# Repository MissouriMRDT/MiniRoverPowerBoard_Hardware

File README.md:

# MiniRoverPowerBoard_Hardware
This repository holds the files to build a Mini Rover that is used during PR events.

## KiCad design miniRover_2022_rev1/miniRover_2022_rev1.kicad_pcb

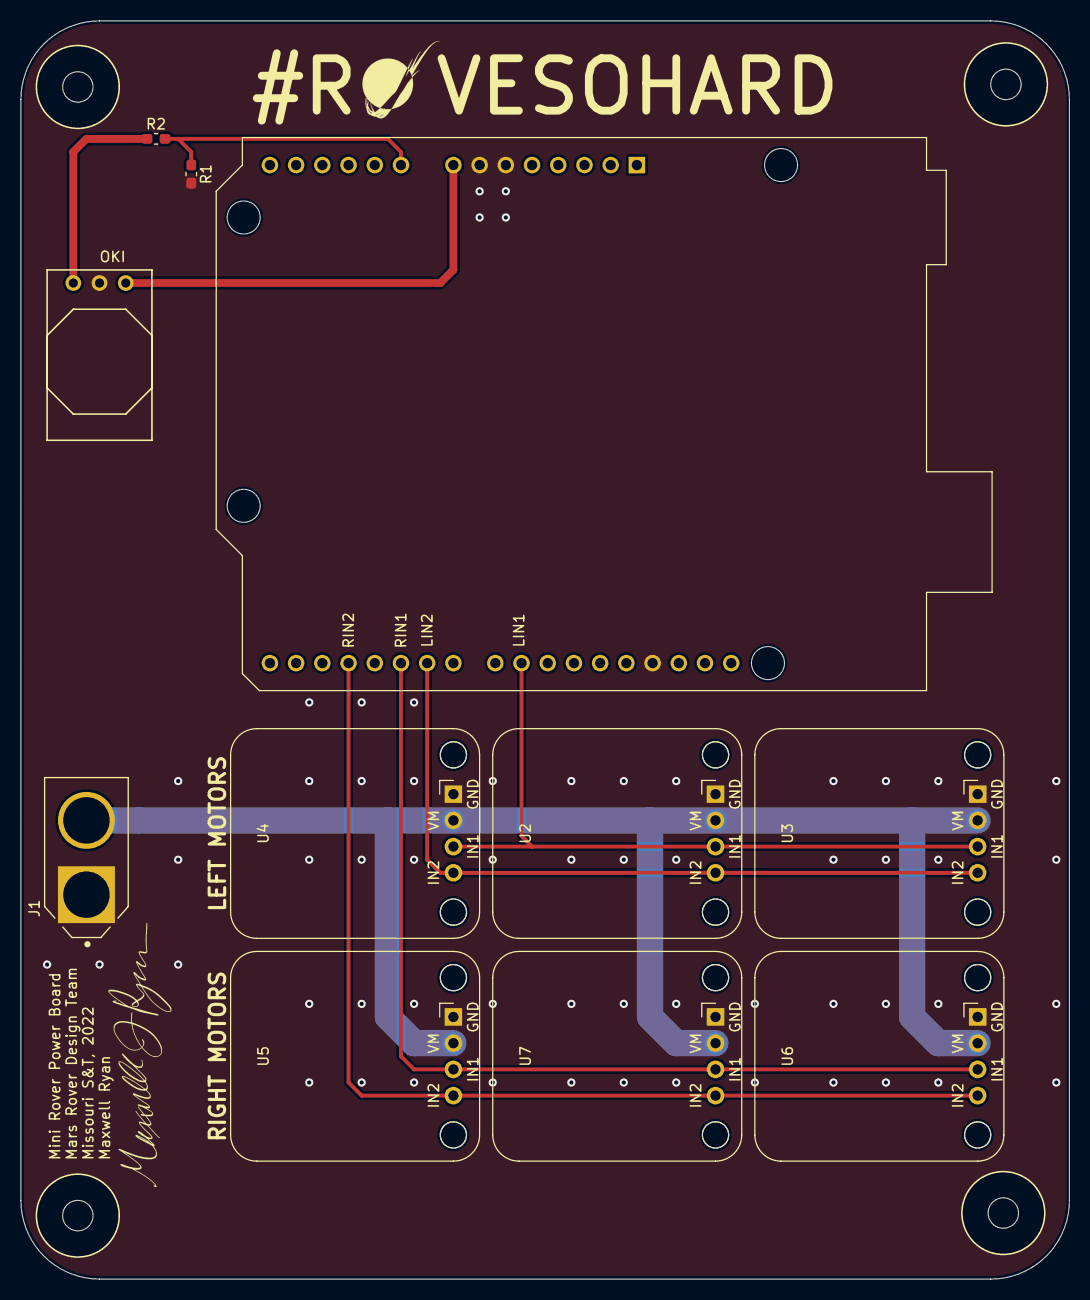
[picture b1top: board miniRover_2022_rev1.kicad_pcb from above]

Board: 2 copper layers, 101.6 x 121.9 mm, 11 parts (1 on the bottom side), 8 nets.

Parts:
A1: Arduino_UNO_R3; Arduino_UNO_R3_WithMountingHoles
J1: XT60-M; AMASS_XT60-M
R1: 1k; R_0603_1608Metric_Pad1.05x0.95mm_HandSolder
R2: 2k; R_0603_1608Metric_Pad1.05x0.95mm_HandSolder
U1: OKI; OKI_Horizontal
U2, U3, U4, U5, U6, U7: DRV8871-Breakout-PCB

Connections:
+5V: A1.8, U1.3
+12V: J1.2, R2.1, U1.1, U2.2, U3.2, U4.2, U5.2, U6.2, U7.2
/motorControllers/LIN1: A1.24, U2.3, U3.3, U4.3
/motorControllers/LIN2: A1.21, U2.4, U3.4, U4.4
/motorControllers/RIN1: A1.20, U5.3, U6.3, U7.3
/motorControllers/RIN2: A1.18, U5.4, U6.4, U7.4
GND: A1.6, A1.7, A1.29, J1.1, R1.2, U1.2, U2.1, U3.1, U4.1, U5.1, U6.1, U7.1
unnamed: A1.9, R1.1, R2.2

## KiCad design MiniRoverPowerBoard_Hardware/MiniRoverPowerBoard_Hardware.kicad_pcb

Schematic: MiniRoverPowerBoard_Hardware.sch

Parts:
B1: Buzzer; BUZZER_SMI_1324_TW_5V_2_R
C1, C4, C8, C9, C10, C11, C12: 10u; C_0603_1608Metric_Pad1.05x0.95mm_HandSolder
C2: 1n; C_0603_1608Metric_Pad1.05x0.95mm_HandSolder
C5, C6: 470u; CP_Radial_D8.0mm_P3.50mm
Conn1, Conn2, Conn3, Conn4: AndersonPP; Anderson_2_Horizontal_Side_by_Side
Conn5: E_STOP; MOLEX_SL_02_Vertical
Conn6: Molex_SL_07; MOLEX_SL_07_Vertical
Conn7: Molex_SL_03; MOLEX_SL_03_Vertical
Conn8: Molex_SL_02; MOLEX_SL_02_Vertical
Conn9, Conn10: Molex_SL_04; MOLEX_SL_04_Vertical
D1, D9: 4.7V_Zener; D_SOD-123
D2, D3, D4, D5, D6, D10, D11: LED; LED_0603_1608Metric_Pad1.05x0.95mm_HandSolder
D8: D_Schottky; D_0603_1608Metric_Pad1.05x0.95mm_HandSolder
F1: 35A_Fuse; ATC_Fuse_Block
L2: 47uH; CP_Radial_D5.0mm_P2.00mm
Q1, Q2, Q4: Q_NMOS_GSD; SOT-323_SC-70_Handsoldering
Q3: Q_PMOS_GDS; TO-252-2
R1, R2, R3, R4, R5, R6: 1k; R_0603_1608Metric_Pad1.05x0.95mm_HandSolder
R7, R10, R13, R14, R25: 10k; R_0603_1608Metric_Pad1.05x0.95mm_HandSolder
R8, R22: 21k; R_0603_1608Metric_Pad1.05x0.95mm_HandSolder
R9, R23: 26.7k; R_0603_1608Metric_Pad1.05x0.95mm_HandSolder
R11: 30k; R_0603_1608Metric_Pad1.05x0.95mm_HandSolder
R12: 13k; R_0603_1608Metric_Pad1.05x0.95mm_HandSolder
R15, R26: 0; R_0603_1608Metric_Pad1.05x0.95mm_HandSolder
R16, R17, R19, R20, R21, R24: 510; R_0603_1608Metric_Pad1.05x0.95mm_HandSolder
R18: 100; R_0603_1608Metric_Pad1.05x0.95mm_HandSolder
SW1: Relay_SPST; MOLEX_SL_04_Vertical
SW2, SW3: SW_Push; SW_SPST_TL3305A
U1, U2: VNH5019A_E; MultiPowerSO_30
U3: ACS722xLCTR-40AU; SOIC-8_3.9x4.9mm_P1.27mm
U5: AP1509; SOIC-8_3.9x4.9mm_P1.27mm
U6: ARDUINO_MICRO_SHIELD

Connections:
+3V3: C1.2, R18.1, U1.5, U1.6, U1.9, U2.5, U2.6, U2.9, U3.8 (VCC), U6.3.3V
+5V: B1.1, C8.1, Conn6.1, Conn8.1, L2.2, R17.1, R26.2, SW1.2, SW2.1, SW3.1, U5.3
/5V_R: R26.1, U6.5V
/PVDD_IN1: Conn1.2, Conn2.2, F1.2
/PVDD_IN2: F1.1, U3.1 (IP+), U3.2 (IP+)
/PVDD_IN3: Q3.3, R11.1, SW1.3, U3.3 (IP-), U3.4 (IP-)
/VIN_R: R15.1, U6.VI
ACT_PWR: C5.1, C6.1, C9.1, C10.1, C11.1, C12.1, Conn9.1, Conn9.2, Conn10.1, Conn10.2, Q3.2, R16.1, R22.1, U1.3, U1.12, U1.13, U1.23, U1.32, U2.3, U2.12, U2.13, U2.23, U2.32
BUZZER_EN: Q4.1, R25.2, U6.2
CONTROLLER_ATT: Conn6.6, U6.A1
CONTROLLER_CLK: Conn6.4, U6.13
CONTROLLER_CMD: Conn6.5, U6.A0
CONTROLLER_DAT: Conn6.7, U6.A2
ESTOP_EN: Conn5.1, U6.3
GND: C1.1, C2.1, C4.2, C5.2, C6.2, C8.2, C9.2, C10.2, C11.2, C12.2, Conn1.1, Conn2.1, Conn6.2, Conn7.3, Conn8.2, Conn9.3, Conn9.4, Conn10.3, Conn10.4, D1.2, D2.1, D3.1, D4.1, D5.1, D6.1, D8.2, D9.2, D10.1, D11.1, Q1.2, Q2.2, Q4.2, R7.2, R9.2, R10.2, R13.2, R14.2, R23.2, R25.1, U1.18, U1.19, U1.20, U1.26, U1.27, U1.28, U2.18, U2.19, U2.20, U2.26, U2.27, U2.28, U3.5 (GND), U5.4, U5.5, U5.6, U5.7, U5.8, U6.GND
IN_A1: R1.1, U6.5
IN_A2: R4.1, U6.8
IN_B1: R3.1, U6.7
IN_B2: R6.1, U6.10
LEFT_PWM: R2.1, U6.6
LEFT_SW: R13.1, SW2.2, U6.12
LOGIC_PWR: C4.1, R8.1, R15.2, SW1.4, U5.1
LOG_SW_EN: Q1.1, R7.1, U6.4
unnamed: B1.2, Q4.3
unnamed: C2.2, U3.6 (BW_SEL)
unnamed: Conn5.2, Q2.1, R10.1
unnamed: D2.2, R16.2
unnamed: D3.2, R17.2
unnamed: D4.2, R18.2
unnamed: D5.2, R19.2
unnamed: D6.2, R20.2
unnamed: D8.1, L2.1, U5.2
unnamed: D10.2, R21.2
unnamed: D11.2, R24.2
unnamed: Q1.3, SW1.1
unnamed: Q2.3, R12.2
unnamed: Q3.1, R11.2, R12.1
unnamed: R1.2, U1.4
unnamed: R2.2, U1.7
unnamed: R3.2, U1.10
unnamed: R4.2, U2.4
unnamed: R5.2, U2.7
unnamed: R6.2, U2.10
OUT_A_LEFT: Conn3.1, R19.1, U1.1, U1.25, U1.30, U1.31
OUT_A_RIGHT: Conn4.1, R21.1, U2.1, U2.25, U2.30, U2.31
OUT_B_LEFT: Conn3.2, R20.1, U1.15, U1.16, U1.21, U1.33
OUT_B_RIGHT: Conn4.2, R24.1, U2.15, U2.16, U2.21, U2.33
PACK_IMEAS: U3.7 (VIOUT), U6.A5
RIGHT_PWM: R5.1, U6.9
RIGHT_SW: R14.1, SW3.2, U6.11
RX: Conn7.2, U6.RX
TX: Conn7.1, U6.TX
V_ACT_SENSE: D9.1, R22.2, R23.1, U6.A4
V_LOG_SENSE: D1.1, R8.2, R9.1, U6.A3

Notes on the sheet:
Power Control
Input
Current Measurment
Logic Power Switch
E-Stop
Output
Microcontroller
Buzzer
Drive Switches
Indication
Green
Left Motors
Right Motors
Motor Drivers
Orange
8.4V Max 7.4V Nominal 5.0V Min (Broken)
8.4V to 4.7V
16mA
13mA
10mA
Min Input Voltage: 4.5V 500mA limit due to inductor
5V Regulation
Controller Conn
Min Input Volatge: 7V
8.4V to 2.54V 6V to 1.81V
Serial Conn
Extra Outputs
12V
Sorry for these 12V connectors. Whole andersons for 12V extra busses on a mini rover are overkill. But I don't want to introduce a new connector outside our standards. So two pins on a Molex SL will get you 4A.

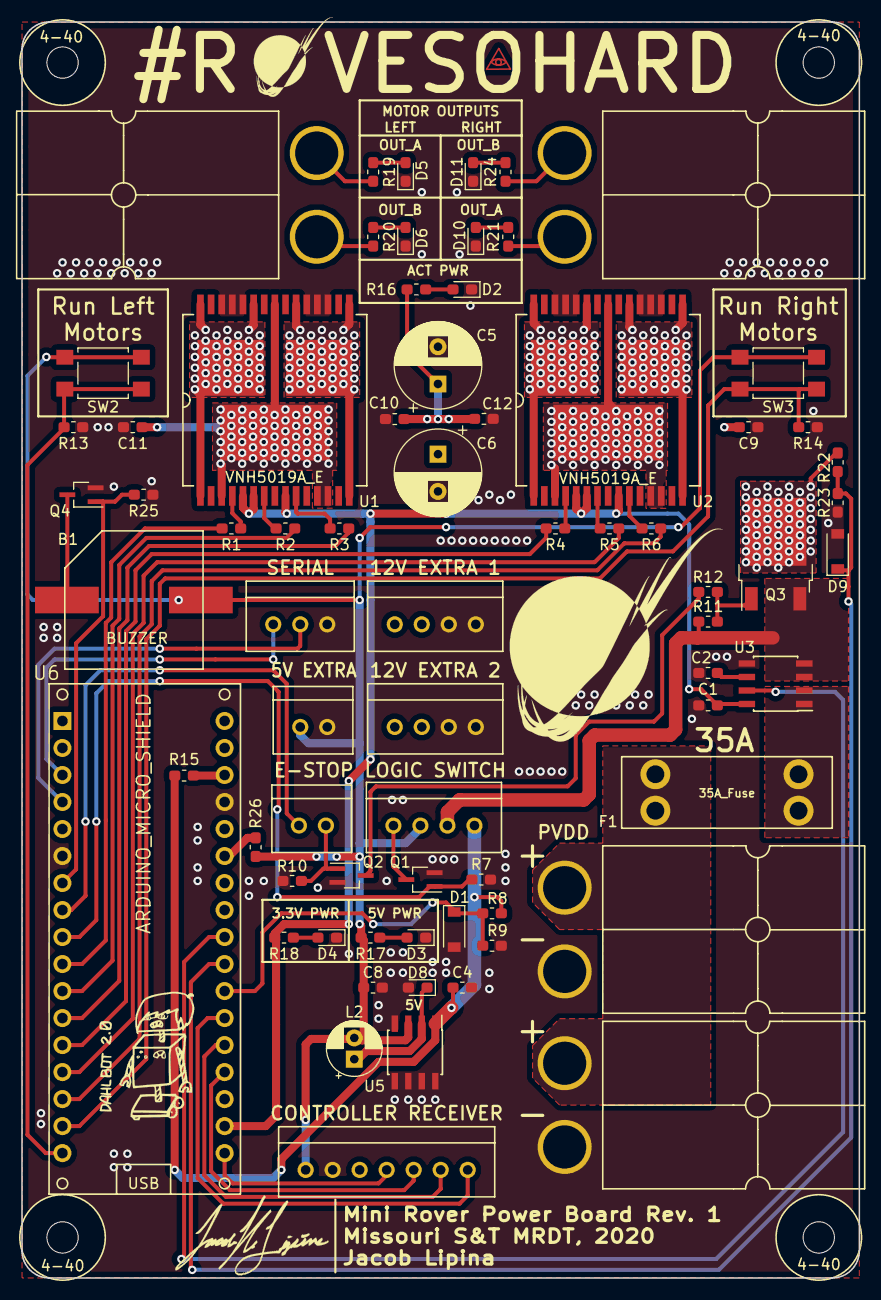
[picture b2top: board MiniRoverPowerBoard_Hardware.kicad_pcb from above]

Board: 2 copper layers, 78.7 x 118.1 mm, 71 parts (0 on the bottom side), 54 nets.

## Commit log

2019-10-25 Started Project and Schematic
2019-10-25 Finished Power Control, Started uC
2019-11-09 Added motor drivers, 3v3 buck, sw, uC assignments
    Next is to add remote control
2019-11-09 Added Controller Conn and Pins on uC
2019-11-13 Footprints assigned to symbols; Netlist generated
2019-11-13 All footprints correct and layout started
2019-11-14 Almost All Components Layed Out
2019-11-14 All Comps Placed; Adding more though :(
2019-11-21 Added Extra Buses & Started Polygons
2019-11-24 Majority of routing complete; few buses to go
2019-11-24 Layout & silkscreen complete; Ready for review
2019-12-11 Removed 3v3 AP1509 and changed voltage dividers
2019-12-13 Finished board changes for arduino pwr & added gerbs
2019-12-14 Finished BOM
2021-07-13 file structure and miniRover_2022_rev1 kicad project created
2021-07-13 mocos , oki, xt60 added to schematic
    added xt60 lib&footprint
2021-07-13 gnd planes added
2021-07-13 rev1 finished, will be reviewing over the following days
2021-07-14 fixed arduino footprint issue
    created proper netlist

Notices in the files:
parts and their libraries:
Copyright 2016 Accelerated Designs. All rights reserved.
